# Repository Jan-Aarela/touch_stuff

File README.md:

# **Touch Stuff**

<table>
  <thead>
    <tr>
      <th colspan="2" align="left"><strong>TRACKPAD R2</strong></th>
    </tr>
    <tr>
      <th align="left" > FRONT</th>
      <th align="left" > BACK</th>
    </tr>
  </thead>
  <tbody>
    <tr>
      <td></td>
      <td></td>
    </tr>
  </tbody>
</table>

<table>
  <thead>
    <tr>
      <th colspan="2" align="left"><strong>TRACKPAD R1</strong></th>
    </tr>
    <tr>
      <th align="left"> FRONT</th>
      <th align="left"> BACK</th>
    </tr>
  </thead>
  <tbody>
    <tr>
      <td></td>
      <td></td>
    </tr>
  </tbody>
</table>

<table>
  <thead>
    <tr>
      <th colspan="2" align="left"><strong>CAP-PADS</strong></th>
    </tr>
    <tr>
      <th align="left"> FRONT</th>
      <th align="left"> BACK</th>
    </tr>
  </thead>
  <tbody>
    <tr>
      <td></td>
      <td></td>
    </tr>
  </tbody>
</table>

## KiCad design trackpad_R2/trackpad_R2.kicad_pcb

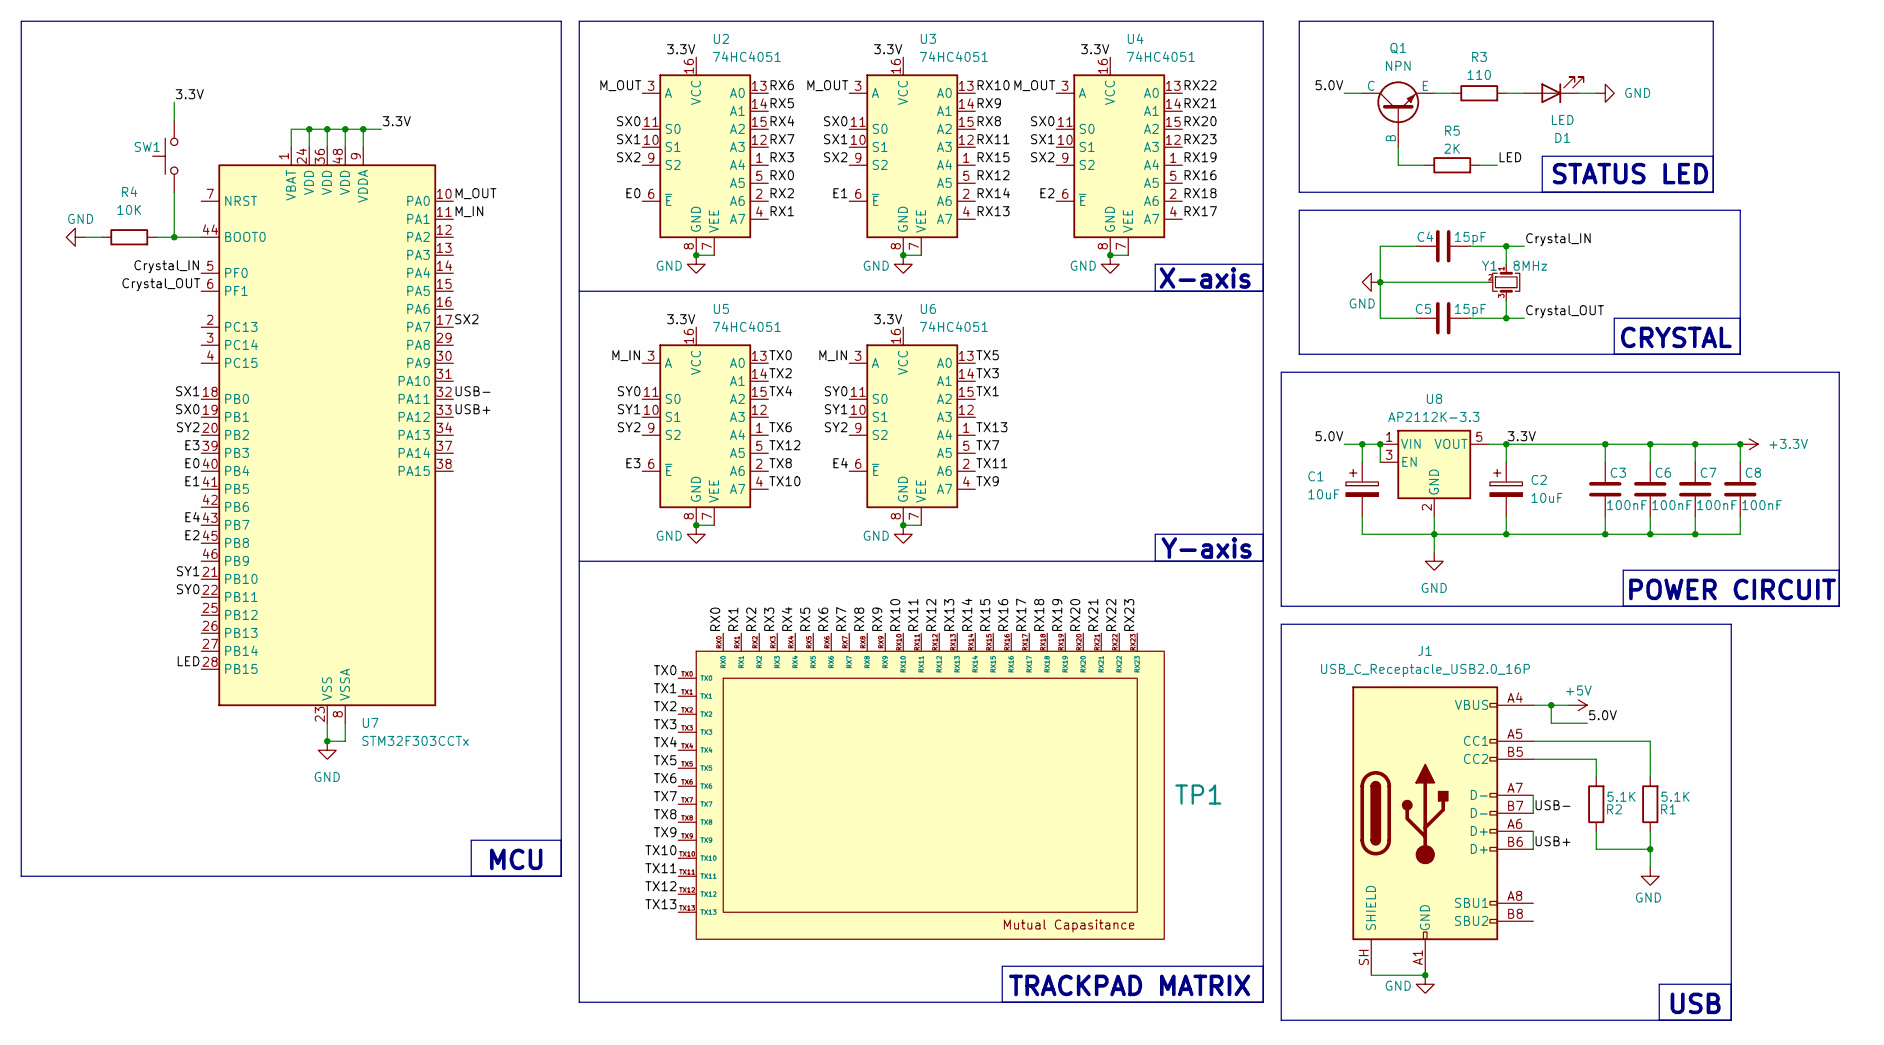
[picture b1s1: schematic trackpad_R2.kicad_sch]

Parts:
C1, C2: 10uF; C_0805_2012Metric
C3, C6, C7, C8: 100nF; C_0603_1608Metric_Pad1.08x0.95mm_HandSolder
C4, C5: 15pF; C_0603_1608Metric_Pad1.08x0.95mm_HandSolder
D1: LED; LED_1206_3216Metric_ReverseMount_Hole1.8x2.4mm
J1: USB_C_Receptacle_USB2.0_16P; USB_C_Receptacle_GCT_USB4105-xx-A_16P_TopMnt_Horizontal
Q1: NPN; SOT-323_SC-70
R1, R2: 5.1K; R_0603_1608Metric_Pad0.98x0.95mm_HandSolder
R3: 110; R_0603_1608Metric_Pad0.98x0.95mm_HandSolder
R4: 10K; R_0603_1608Metric_Pad0.98x0.95mm_HandSolder
R5: 2K; R_0603_1608Metric_Pad0.98x0.95mm_HandSolder
SW1: SW_Omron_B3FS; SW_Push_1P1T_NO_CK_KMR2
TP1: trackpad_24x14_132mm_77mm
U2, U3, U4, U5, U6: 74HC4051; SOIC-16_3.9x9.9mm_P1.27mm
U7: STM32F303CCTx; LQFP-48_7x7mm_P0.5mm
U8: AP2112K-3.3; SOT-23-5
Y1: 8MHz; Crystal_SMD_Abracon_ABM8G-4Pin_3.2x2.5mm

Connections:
+3.3V: C2.1, C3.1, C6.1, C7.1, C8.1, SW1.2, U2.16 (VCC), U3.16 (VCC), U4.16 (VCC), U5.16 (VCC), U6.16 (VCC), U7.1 (VBAT), U7.9 (VDDA), U7.24 (VDD), U7.36 (VDD), U7.48 (VDD), U8.5 (VOUT)
+5V: C1.1, J1.A4 (VBUS), J1.A9 (VBUS), J1.B4 (VBUS), J1.B9 (VBUS), Q1.1 (C), U8.1 (VIN), U8.3 (EN)
/Crystal_IN: C4.2, U7.5 (PF0), Y1.1
/Crystal_OUT: C5.2, U7.6 (PF1), Y1.3
/E0: U2.6 (~E), U7.40 (PB4)
/E1: U3.6 (~E), U7.41 (PB5)
/E2: U4.6 (~E), U7.45 (PB8)
/E3: U5.6 (~E), U7.39 (PB3)
/E4: U6.6 (~E), U7.43 (PB7)
/LED: R5.2, U7.28 (PB15)
/M_IN: U5.3 (A), U6.3 (A), U7.11 (PA1)
/M_OUT: U2.3 (A), U3.3 (A), U4.3 (A), U7.10 (PA0)
/RX0: TP1.RX0, U2.5 (A5)
/RX1: TP1.RX1, U2.4 (A7)
/RX2: TP1.RX2, U2.2 (A6)
/RX3: TP1.RX3, U2.1 (A4)
/RX4: TP1.RX4, U2.15 (A2)
/RX5: TP1.RX5, U2.14 (A1)
/RX6: TP1.RX6, U2.13 (A0)
/RX7: TP1.RX7, U2.12 (A3)
/RX8: TP1.RX8, U3.15 (A2)
/RX9: TP1.RX9, U3.14 (A1)
/RX10: TP1.RX10, U3.13 (A0)
/RX11: TP1.RX11, U3.12 (A3)
/RX12: TP1.RX12, U3.5 (A5)
/RX13: TP1.RX13, U3.4 (A7)
/RX14: TP1.RX14, U3.2 (A6)
/RX15: TP1.RX15, U3.1 (A4)
/RX16: TP1.RX16, U4.5 (A5)
/RX17: TP1.RX17, U4.4 (A7)
/RX18: TP1.RX18, U4.2 (A6)
/RX19: TP1.RX19, U4.1 (A4)
/RX20: TP1.RX20, U4.15 (A2)
/RX21: TP1.RX21, U4.14 (A1)
/RX22: TP1.RX22, U4.13 (A0)
/RX23: TP1.RX23, U4.12 (A3)
/SX0: U2.11 (S0), U3.11 (S0), U4.11 (S0), U7.19 (PB1)
/SX1: U2.10 (S1), U3.10 (S1), U4.10 (S1), U7.18 (PB0)
/SX2: U2.9 (S2), U3.9 (S2), U4.9 (S2), U7.17 (PA7)
/SY0: U5.11 (S0), U6.11 (S0), U7.22 (PB11)
/SY1: U5.10 (S1), U6.10 (S1), U7.21 (PB10)
/SY2: U5.9 (S2), U6.9 (S2), U7.20 (PB2)
/TX0: TP1.TX0, U5.13 (A0)
/TX1: TP1.TX1, U6.15 (A2)
/TX2: TP1.TX2, U5.14 (A1)
/TX3: TP1.TX3, U6.14 (A1)
/TX4: TP1.TX4, U5.15 (A2)
/TX5: TP1.TX5, U6.13 (A0)
/TX6: TP1.TX6, U5.1 (A4)
/TX7: TP1.TX7, U6.5 (A5)
/TX8: TP1.TX8, U5.2 (A6)
/TX9: TP1.TX9, U6.4 (A7)
/TX10: TP1.TX10, U5.4 (A7)
/TX11: TP1.TX11, U6.2 (A6)
/TX12: TP1.TX12, U5.5 (A5)
/TX13: TP1.TX13, U6.1 (A4)
/USB+: J1.A6 (D+), J1.B6 (D+), U7.33 (PA12)
/USB-: J1.A7 (D-), J1.B7 (D-), U7.32 (PA11)
GND: C1.2, C2.2, C3.2, C4.1, C5.1, C6.2, C7.2, C8.2, D1.1 (K), J1.A1 (GND), J1.A12 (GND), J1.B1 (GND), J1.B12 (GND), J1.SH (SHIELD), R1.1, R2.1, R4.1, U2.7 (VEE), U2.8 (GND), U3.7 (VEE), U3.8 (GND), U4.7 (VEE), U4.8 (GND), U5.7 (VEE), U5.8 (GND), U6.7 (VEE), U6.8 (GND), U7.8 (VSSA), U7.23 (VSS), U7.35 (VSS), U7.47 (VSS), U8.2 (GND), Y1.2 (G), Y1.4 (G)
unnamed: D1.2 (A), R3.2
unnamed: J1.A5 (CC1), R1.2
unnamed: J1.B5 (CC2), R2.2
unnamed: Q1.2 (B), R5.1
unnamed: Q1.3 (E), R3.1
unnamed: R4.2, SW1.1, U7.44 (BOOT0)

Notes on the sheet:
STATUS LED
X-axis
POWER CIRCUIT
USB
CRYSTAL
TRACKPAD MATRIX
Y-axis
MCU

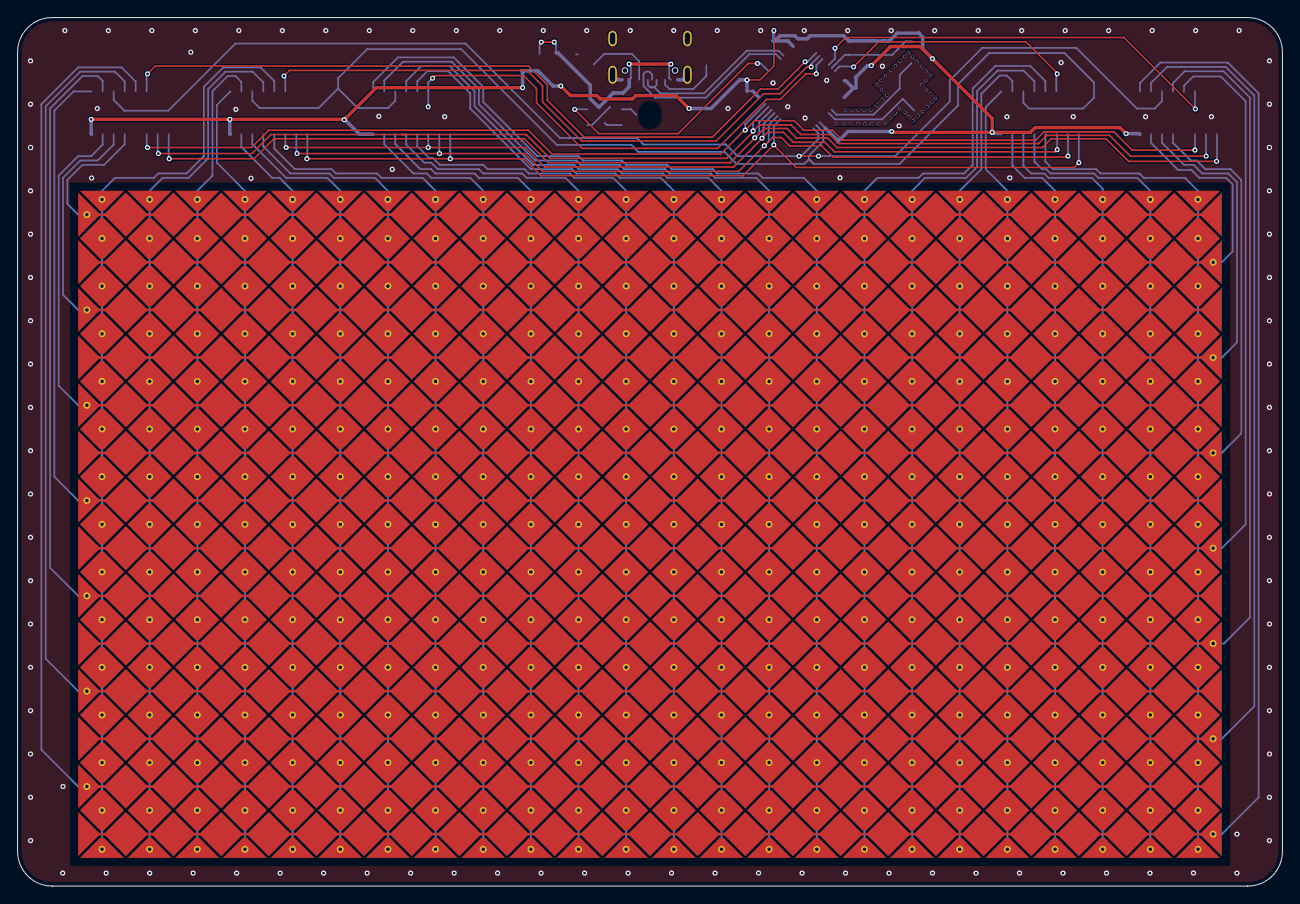
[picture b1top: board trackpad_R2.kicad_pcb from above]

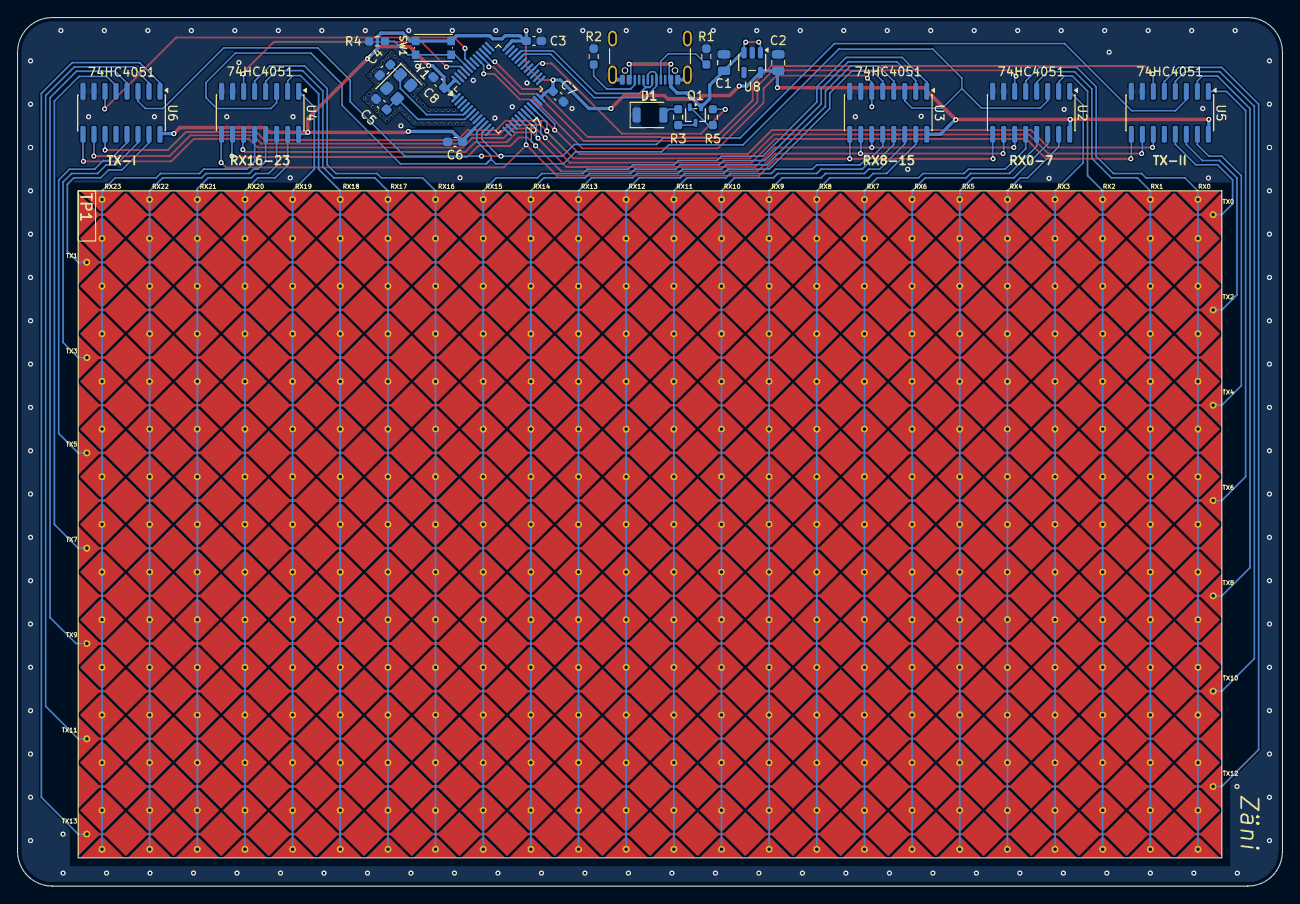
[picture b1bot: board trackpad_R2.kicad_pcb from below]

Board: 2 copper layers, 146.0 x 100.2 mm, 26 parts (25 on the bottom side), 65 nets.

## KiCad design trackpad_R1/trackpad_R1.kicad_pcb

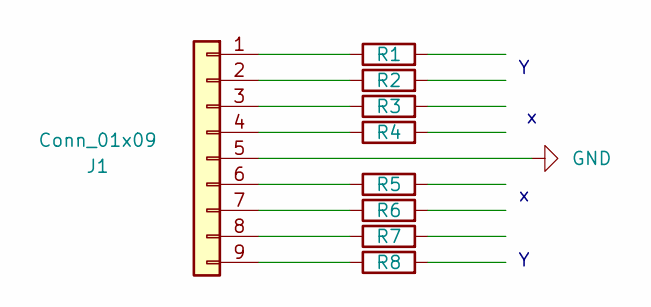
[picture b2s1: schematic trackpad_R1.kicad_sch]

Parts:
J1: Conn_01x09; PinHeader_1x09_P2.54mm_Horizontal
R1, R2, R3, R4, R5, R6, R7: R; R_1206_3216Metric_Pad1.30x1.75mm_HandSolder_extra
R8: R; R_1206_3216Metric_Pad1.30x1.75mm_HandSolder

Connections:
GND: J1.5
unnamed: J1.1, R1.1
unnamed: J1.2, R2.1
unnamed: J1.3, R3.1
unnamed: J1.4, R4.1
unnamed: J1.6, R5.1
unnamed: J1.7, R6.1
unnamed: J1.8, R7.1
unnamed: J1.9, R8.1

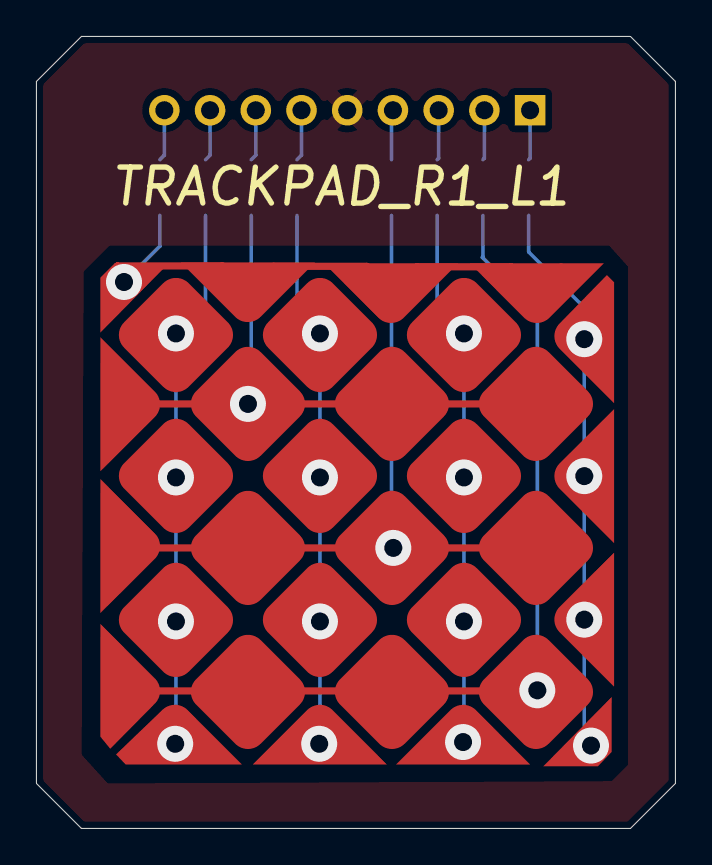
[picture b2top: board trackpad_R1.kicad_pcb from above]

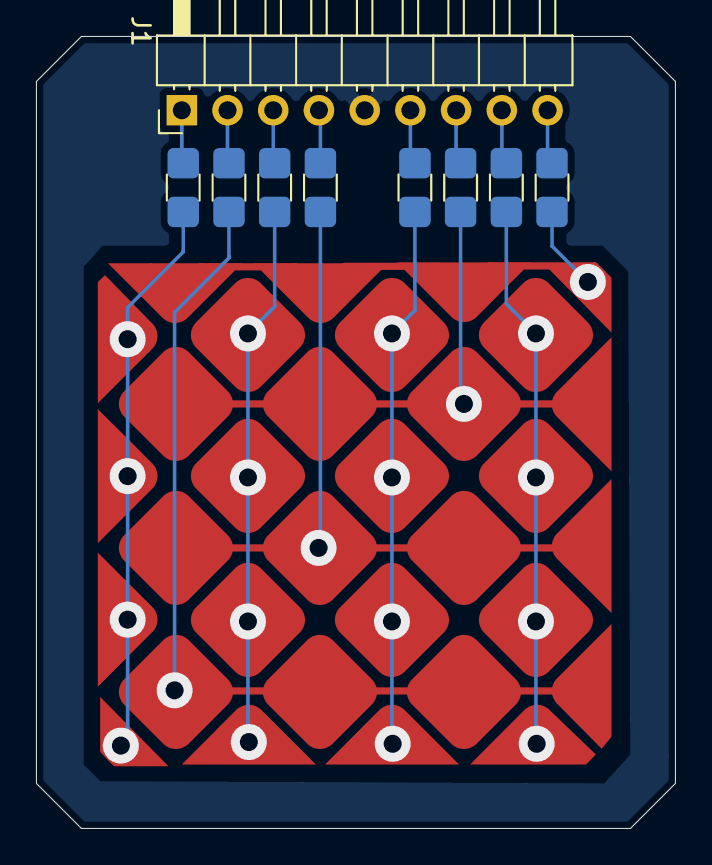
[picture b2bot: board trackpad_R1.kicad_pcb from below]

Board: 2 copper layers, 35.5 x 44.0 mm, 9 parts (9 on the bottom side), 8 nets.

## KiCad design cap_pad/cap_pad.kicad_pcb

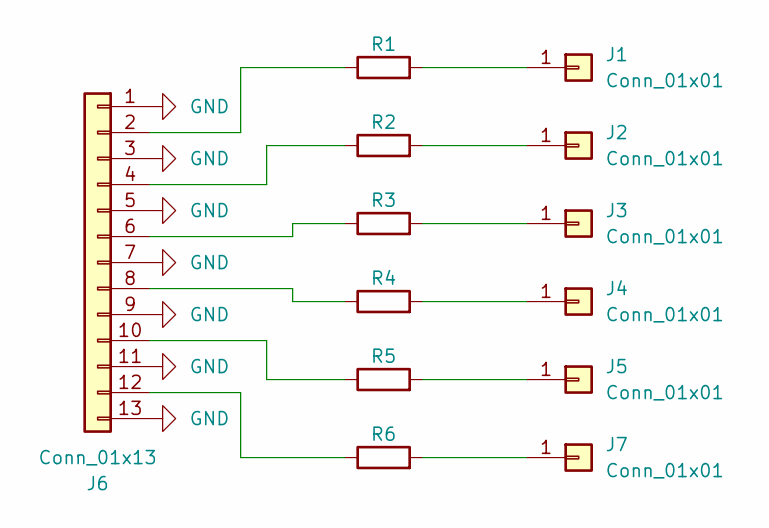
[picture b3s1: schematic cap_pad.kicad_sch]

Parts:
J1, J2, J3, J4, J5, J7: Conn_01x01; testi_padi_15mmx15mm
J6: Conn_01x13; PinHeader_1x13_P2.54mm_Horizontal
R1, R2, R3, R4, R5, R6: R; R_1206_3216Metric_Pad1.30x1.75mm_HandSolder

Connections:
GND: J6.1, J6.3, J6.5, J6.7, J6.9, J6.11, J6.13
unnamed: J1.1 (Pin_1_1), R1.2
unnamed: J2.1 (Pin_1_1), R2.2
unnamed: J3.1 (Pin_1_1), R3.2
unnamed: J4.1 (Pin_1_1), R4.2
unnamed: J5.1 (Pin_1_1), R5.2
unnamed: J6.2, R1.1
unnamed: J6.4, R2.1
unnamed: J6.6, R3.1
unnamed: J6.8, R4.1
unnamed: J6.10, R5.1
unnamed: J6.12, R6.1
unnamed: J7.1 (Pin_1_1), R6.2

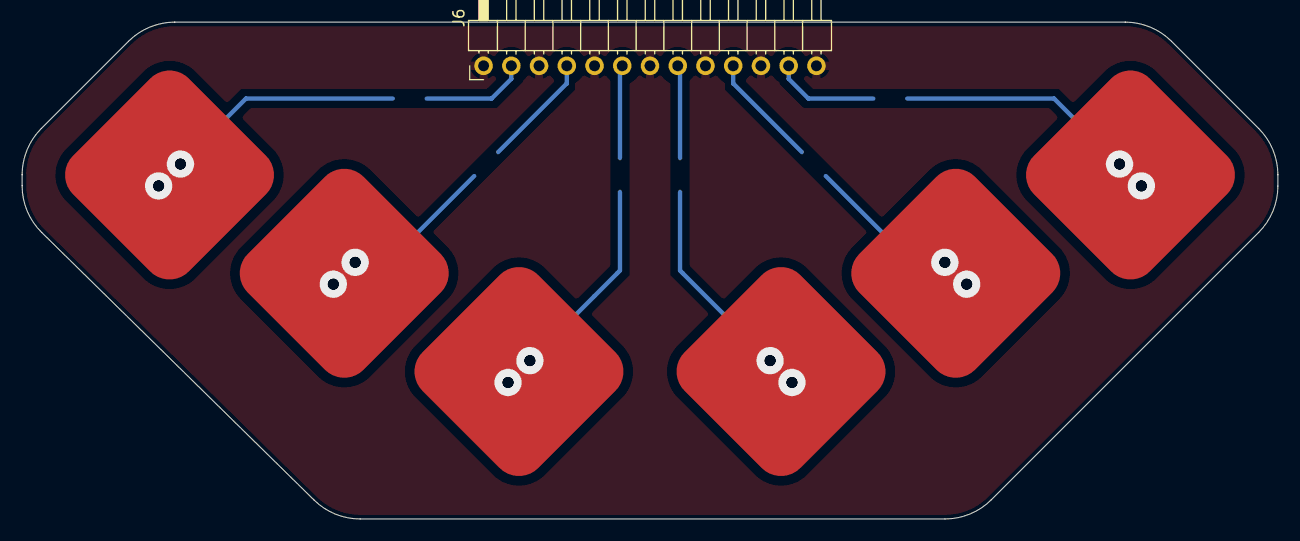
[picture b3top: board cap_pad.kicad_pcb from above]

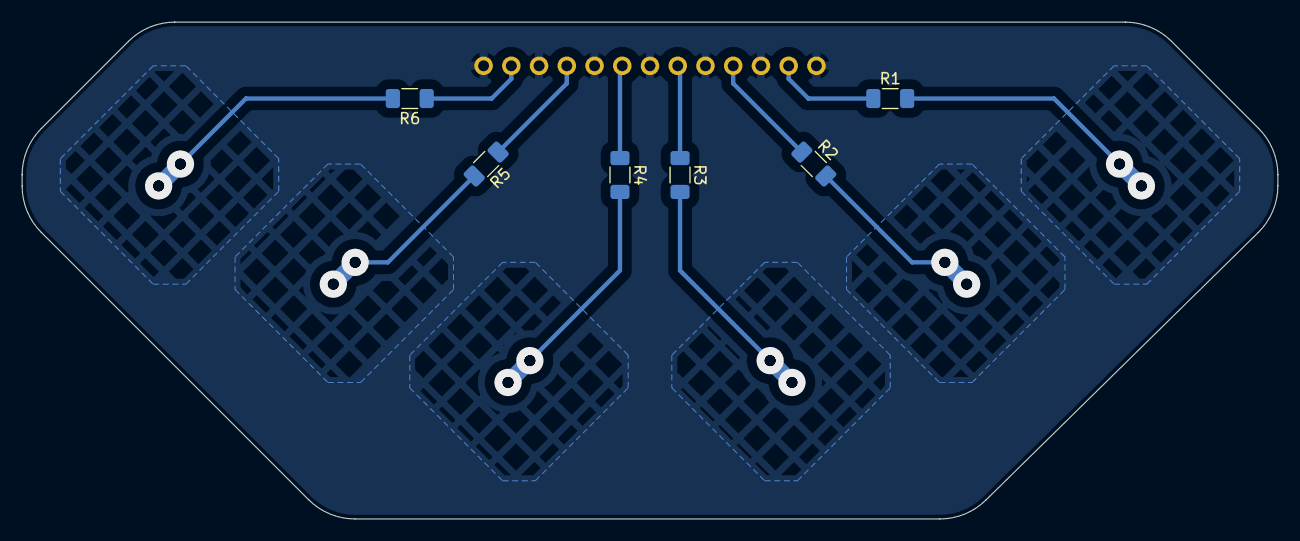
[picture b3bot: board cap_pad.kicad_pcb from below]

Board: 2 copper layers, 115.0 x 45.5 mm, 13 parts (6 on the bottom side), 13 nets.
